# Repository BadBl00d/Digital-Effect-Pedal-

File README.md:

# Guitar Effects Pedal - Capacitive Sensor Project

<div align="center">
    
</div>

This project focuses on the development of a multi-effects pedal for electric guitars. The pedal integrates a capacitive sensor to manipulate audio effects in real time based on the proximity of the user’s foot to a capacitive plate. This is built using the STM32 microcontroller and includes various iconic guitar effects such as tremolo, fuzz, and overdrive.

**The following explanation is only a summarized version of the project. For more details, feel free to consult the report (in French), which explains the operation of each subcomponent in more detail.**

## Features
- **Capacitive Sensor**: The pedal uses a capacitive plate to adjust effect parameters without physical contact, offering a unique and dynamic user interface.
- **Multi-effects**: The pedal supports a range of effects like fuzz, tremolo, and overdrive, with more effects easily implementable through software updates.
- **STM32 Microcontroller**: A STM32F303-K8 microcontroller is responsible for audio signal processing and handling the effects.
- **Custom PCB and 3D Printed Case**: Designed for compactness and ease of use, the pedal features a custom-printed circuit board (PCB) and a 3D-printed case modeled after well-known pedal designs.

## Hardware Overview
- **Capacitive Sensor**: Detects foot proximity to control effects in real time.

<div align="center">
    
    <p><em>Figure 1: Operation of the capacitive sensor.</em></p>
</div>

- **STM32F303-K8**: The microcontroller that manages signal processing and control.

<div align="center">
    
    <p><em>Figure 2: Aspect of the conditionner and STM module.</em></p>
</div>

- **Effect Selector**: A rotary knob to switch between effects.
- **Parameter Adjuster**: A second knob to fine-tune effect parameters.
- **Connectors**: Standard 6.5mm audio jacks for input/output and a USB connector for power and programming.
- **3D Printed Case**: Designed using Inventor and printed using PrusaSlicer.

## Software
The software is written in C and runs on the STM32 platform, leveraging the HAL library for hardware interactions. The effects are implemented using signal processing techniques such as the Fast Fourier Transform (FFT) and digital filters.

<div align="center">
    
    <p><em>Figure 3: Test of the signal loopback on the ADC/DAC. Output signal in yellow.</em></p>
</div>

### Supported Effects
- **Tremolo**: Modulates the volume of the input signal at a user-defined rate.

<div align="center">
    
    <p><em>Figure 4: Test of the tremolo signal.</em></p>
</div>

- **Fuzz/Distortion**: Adds harmonic distortion to the signal for a richer, more aggressive tone.

<div align="center">
    
    <p><em>Figure 5: Test of the distortion signal.</em></p>
</div>

- **Overdrive**: Currently under development, providing a smoother form of distortion.
- **Wah** : Modulates the tone of an audio signal by sweeping through a range of frequencies. 
  
### Future Improvements
- **Effect Variety**: Additional effects can be implemented by updating the software.
- **LCD Display**: Potential to add an LCD for real-time feedback on the selected effect and parameter settings.
- **Improved Sensor Sensitivity**: Increasing the detection range of the capacitive sensor for finer control.

## How to Use
1. **Connect the Pedal**: Plug your guitar into the input jack and connect the output to an amplifier.
2. **Power On**: Use a USB cable to power the pedal and program the microcontroller.
3. **Select Effects**: Use the left rotary knob to select between available effects.
4. **Adjust Parameters**: Modify the intensity or frequency of the effect using the right knob.
5. **Real-Time Control**: Move your foot above the capacitive plate to dynamically alter the effect parameters.

## Setup and Installation
1. **Download the Code**: Clone the repository from GitHub.
2. **Flash the Microcontroller**: Use an ST-Link or USB to flash the STM32F303 with the provided firmware.
3. **Assemble the Hardware**: Follow the instructions in the hardware folder to assemble the pedal and integrate the components.
4. **Test the Pedal**: After assembly, test the pedal with a guitar and amplifier, adjusting the effects using the knobs and capacitive sensor.

## Files and Directories
- **/src**: Contains the main code for the effects and sensor control.
- **/hardware**: Schematics for the custom PCB and 3D printing files for the case.
- **/docs**: Documentation related to the project design and future improvements.

## Acknowledgments
- Inspiration from classic analog pedals such as wah-wah, fuzz, and tremolo.
- Use of STM32F303-K8 microcontroller for audio processing.
- 3D design tools: Inventor and PrusaSlicer for case design and manufacturing.

<div align="center">
    
    <p><em>Figure 6: PrusaSlicer's view of the 3D model.</em></p>
</div>

## Possibilies of improvement 
- Modulate the code to make it cleaner.

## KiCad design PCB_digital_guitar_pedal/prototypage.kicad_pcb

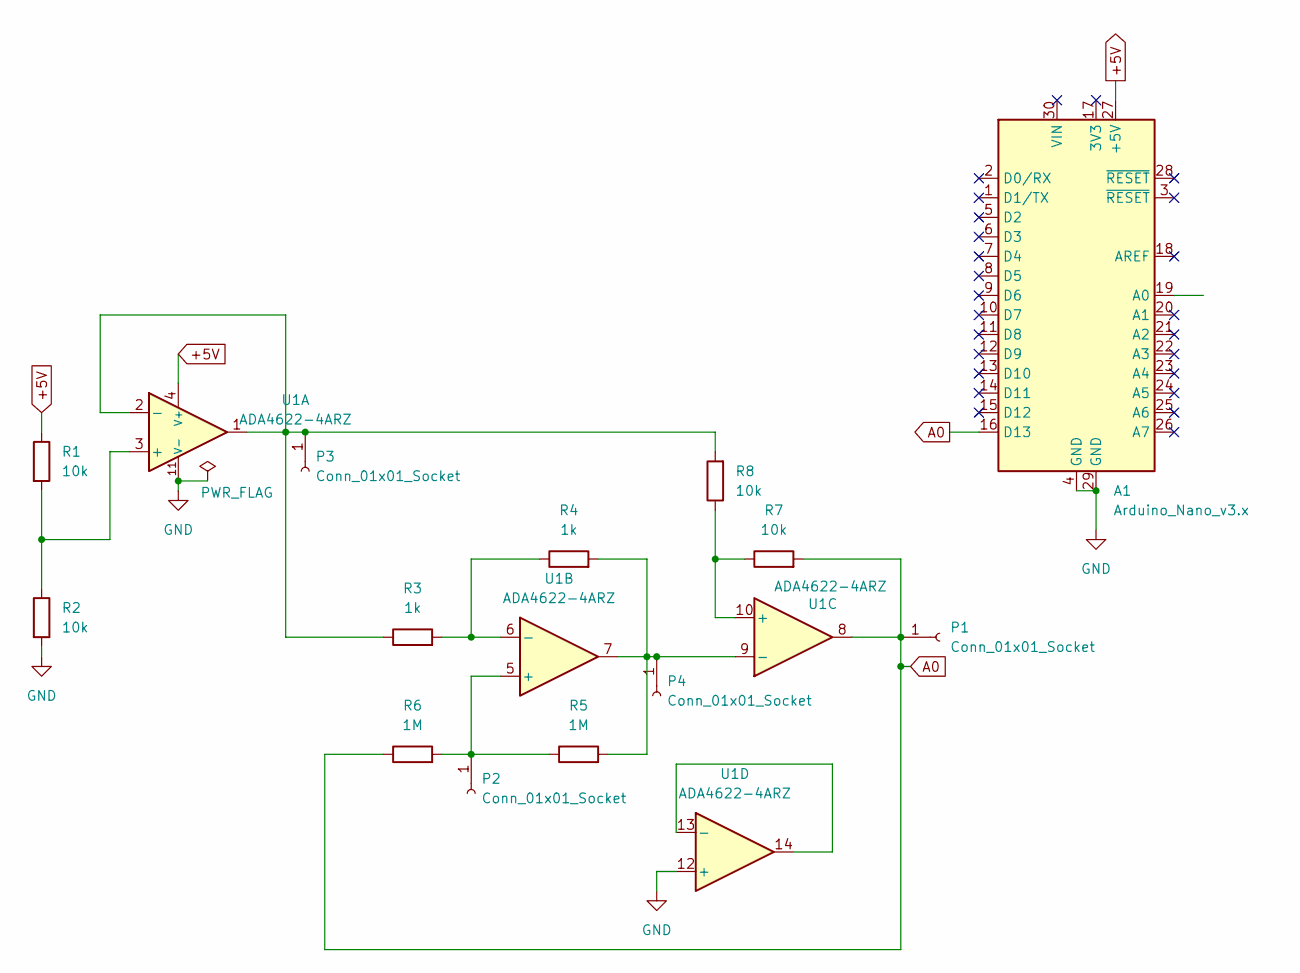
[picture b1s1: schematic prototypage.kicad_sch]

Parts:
A1: Arduino_Nano_v3.x; Arduino_Nano
P1, P2, P3, P4: Conn_01x01_Socket; PinHeader_1x01_P2.54mm_Vertical
R1, R2, R7, R8: 10k; R_0805_2012Metric_Pad1.20x1.40mm_HandSolder
R3, R4: 1k; R_0805_2012Metric_Pad1.20x1.40mm_HandSolder
R5, R6: 1M; R_0805_2012Metric_Pad1.20x1.40mm_HandSolder
U1: ADA4622-4ARZ; SOIC-14_3.9x8.7mm_P1.27mm

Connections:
+5V: A1.27 (+5V), R1.1, U1.4 (V+)
A0: A1.16 (D13), P1.1, R6.1, R7.2, U1.8
GND: A1.4 (GND), A1.29 (GND), R2.2, U1.11 (V-), U1.12 (+)
unnamed: P2.1, R5.1, R6.2, U1.5 (+)
unnamed: P3.1, R3.1, R8.2, U1.1, U1.2 (-)
unnamed: P4.1, R4.2, R5.2, U1.7, U1.9 (-)
unnamed: R1.2, R2.1, U1.3 (+)
unnamed: R3.2, R4.1, U1.6 (-)
unnamed: R7.1, R8.1, U1.10 (+)
unnamed: U1.13 (-), U1.14

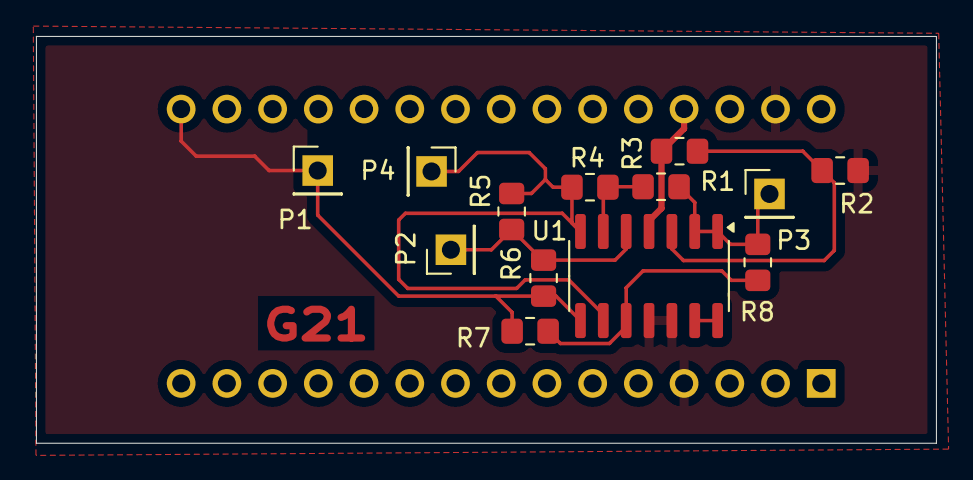
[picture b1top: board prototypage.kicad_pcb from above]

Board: 2 copper layers, 50.0 x 22.6 mm, 14 parts (1 on the bottom side), 10 nets.
